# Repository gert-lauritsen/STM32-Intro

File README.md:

# STM32-Intro

Agenda
+ Grafisk opsætning
+ Debugger
+ Seriel kommunikation
+ SPI
+ Timer
+ ADC
+ USB

Eksemple 1 er en batterimåler, som vi bruger til at vise ADC og timer

Eksemple 2 er en temperaturlogger, som bruges til at demo USB og SPI

Udviklingsværktøjet er [STM32CUBEIDE](https://www.st.com/en/development-tools/stm32cubeide.html)

Det hele kan følges online på [YOUTUBE](https://youtu.be/U5xcWw9ncK8) og Zoom

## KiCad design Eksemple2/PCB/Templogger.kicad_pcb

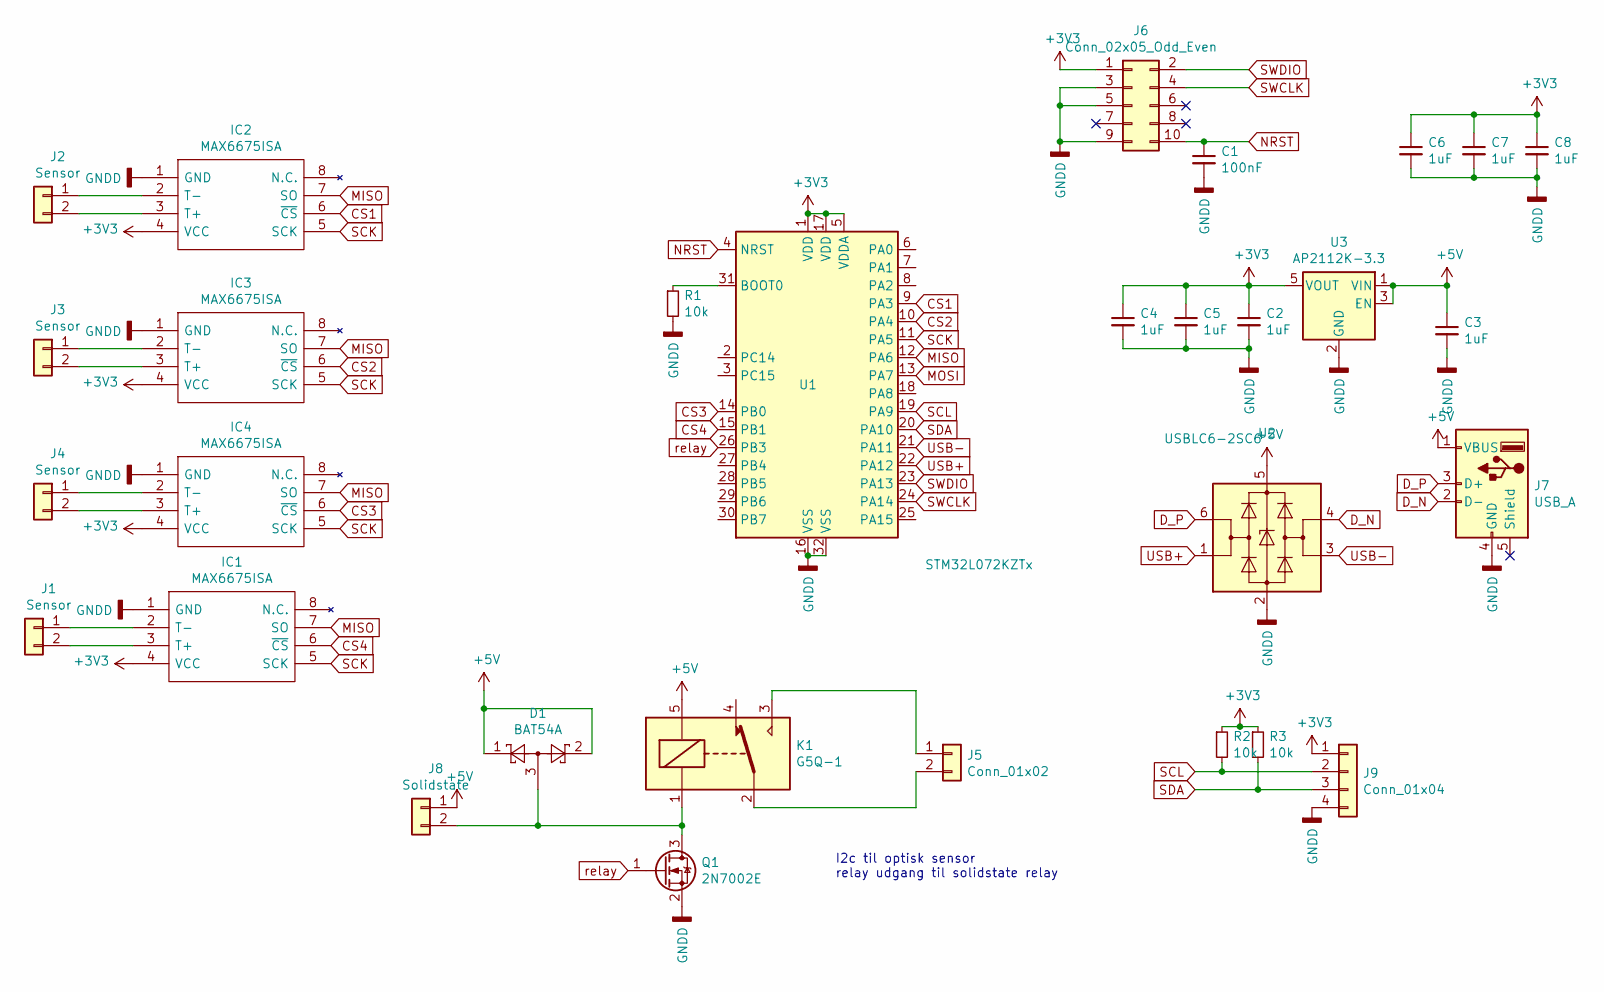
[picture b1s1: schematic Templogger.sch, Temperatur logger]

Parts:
C1: 100nF; C_0805_2012Metric
C2, C3, C4, C5, C6, C7, C8: 1uF; C_0805_2012Metric
D1: BAT54A; SOT-23
IC1, IC2, IC3, IC4: MAX6675ISA; SOIC127P600X175-8N; Mouser Part Number N/A
J1, J2, J3, J4: Sensor; Molex_KK-254_AE-6410-02A_1x02_P2.54mm_Vertical
J5: Conn_01x02; PhoenixContact_MSTBVA_2,5_2-G_1x02_P5.00mm_Vertical
J6: Conn_02x05_Odd_Even; PinHeader_2x05_P1.27mm_Vertical_SMD
J7: USB_A; USB_Mini-B_Wuerth_65100516121_Horizontal
J8: Solidstate; Molex_KK-254_AE-6410-02A_1x02_P2.54mm_Vertical
J9: Conn_01x04; Molex_SL_171971-0004_1x04_P2.54mm_Vertical
K1: G5Q-1; Relay_SPDT_Omron-G5Q-1
Q1: 2N7002E; SOT-23
R1, R2, R3: 10k; R_0805_2012Metric
U1: STM32L072KZTx; LQFP-32_7x7mm_P0.8mm
U2: USBLC6-2SC6; SOT-23-6
U3: AP2112K-3.3; SOT-23-5

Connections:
+3V3: C2.1, C4.1, C5.1, C6.1, C7.1, C8.1, IC1.4 (VCC), IC2.4 (VCC), IC3.4 (VCC), IC4.4 (VCC), J6.1, J9.1, R2.1, R3.1, U1.1 (VDD), U1.5 (VDDA), U1.17 (VDD), U3.5 (VOUT)
+5V: C3.1, D1.1, D1.2, J7.1 (VBUS), J8.1, K1.5, U2.5 (VBUS), U3.1 (VIN), U3.3 (EN)
CS1: IC2.6 (~CS), U1.9 (PA3)
CS2: IC3.6 (~CS), U1.10 (PA4)
CS3: IC4.6 (~CS), U1.14 (PB0)
CS4: IC1.6 (~CS), U1.15 (PB1)
D_N: J7.2 (D-), U2.4 (I/O2)
D_P: J7.3 (D+), U2.6 (I/O1)
GNDD: C1.2, C2.2, C3.2, C4.2, C5.2, C6.2, C7.2, C8.2, IC1.1 (GND), IC2.1 (GND), IC3.1 (GND), IC4.1 (GND), J6.3, J6.5, J6.9, J7.4 (GND), J9.4, Q1.2 (S), R1.2, U1.16 (VSS), U1.32 (VSS), U2.2 (GND), U3.2 (GND)
MISO: IC1.7 (SO), IC2.7 (SO), IC3.7 (SO), IC4.7 (SO), U1.12 (PA6)
NRST: C1.1, J6.10, U1.4 (NRST)
unnamed: D1.3, J8.2, K1.1, Q1.3 (D)
unnamed: IC1.2 (T-), J1.1
unnamed: IC1.3 (T+), J1.2
unnamed: IC2.2 (T-), J2.1
unnamed: IC2.3 (T+), J2.2
unnamed: IC3.2 (T-), J3.1
unnamed: IC3.3 (T+), J3.2
unnamed: IC4.2 (T-), J4.1
unnamed: IC4.3 (T+), J4.2
unnamed: J5.1, K1.3
unnamed: J5.2, K1.2
unnamed: R1.1, U1.31 (BOOT0)
SCK: IC1.5 (SCK), IC2.5 (SCK), IC3.5 (SCK), IC4.5 (SCK), U1.11 (PA5)
SCL: J9.2, R2.2, U1.19 (PA9)
SDA: J9.3, R3.2, U1.20 (PA10)
SWCLK: J6.4, U1.24 (PA14)
SWDIO: J6.2, U1.23 (PA13)
USB+: U1.22 (PA12), U2.1 (I/O1)
USB-: U1.21 (PA11), U2.3 (I/O2)
relay: Q1.1 (G), U1.26 (PB3)

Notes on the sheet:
I2c til optisk sensor relay udgang til solidstate relay

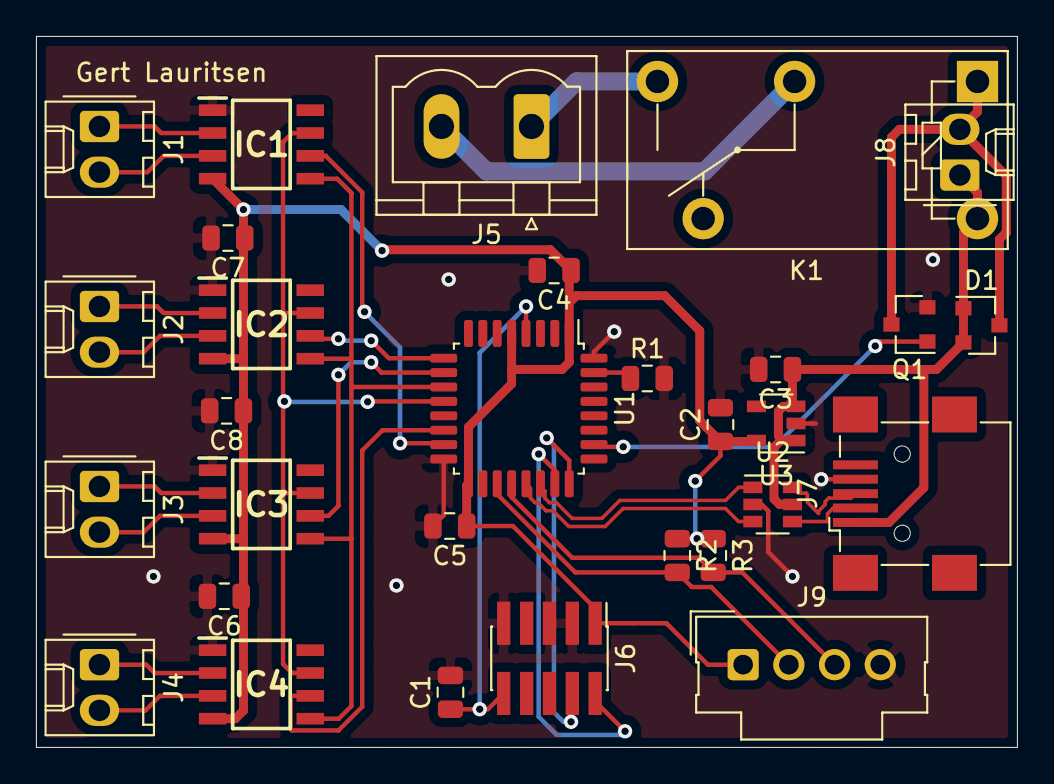
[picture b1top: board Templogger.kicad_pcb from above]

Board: 2 copper layers, 54.5 x 39.5 mm, 30 parts (0 on the bottom side), 31 nets.

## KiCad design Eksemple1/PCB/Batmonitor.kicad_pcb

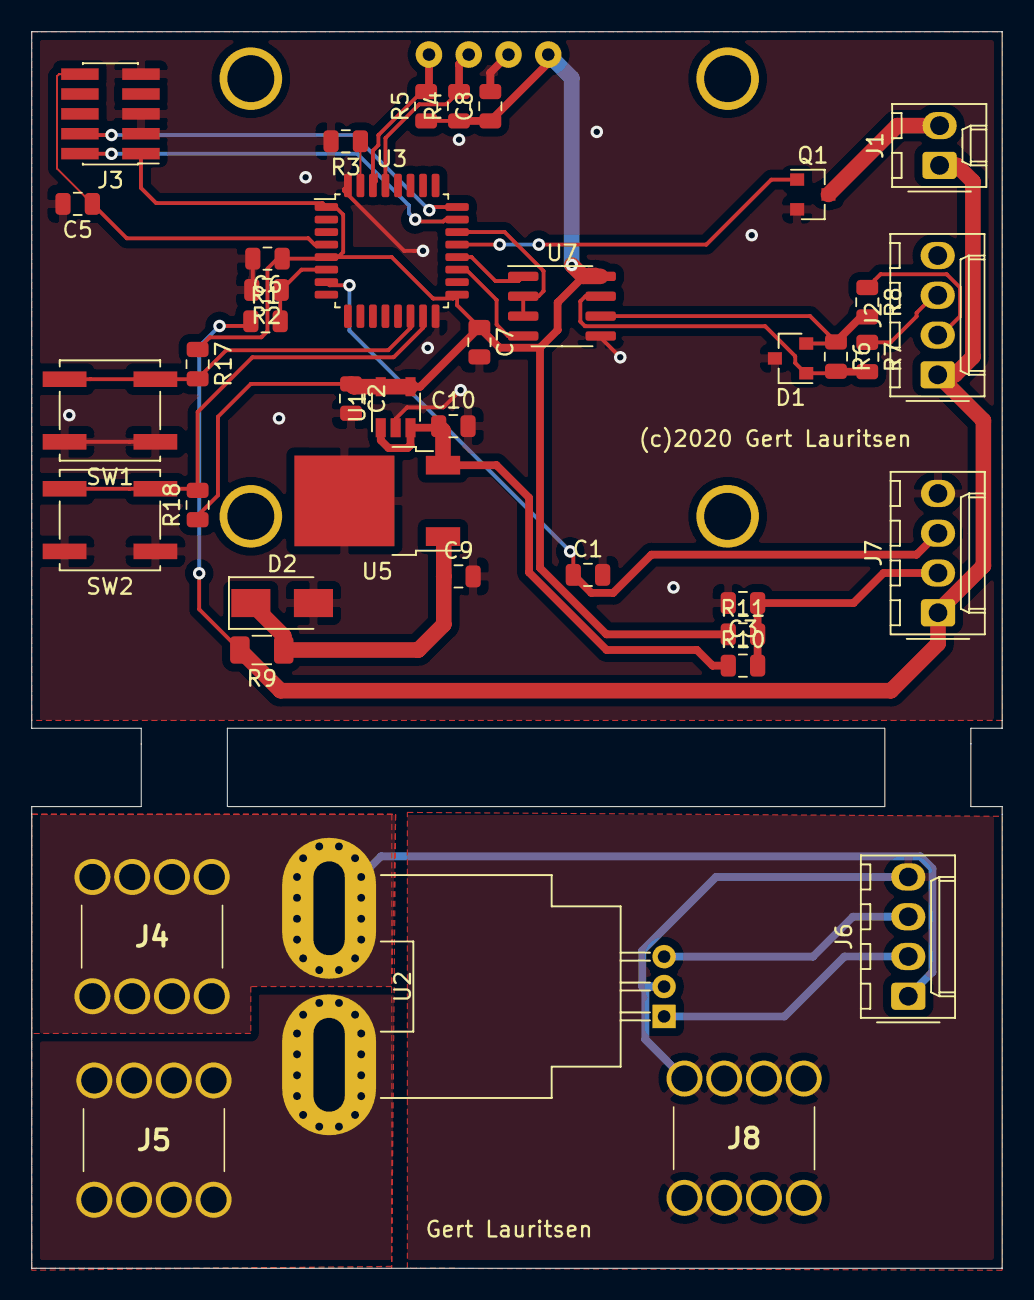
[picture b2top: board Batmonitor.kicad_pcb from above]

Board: 2 copper layers, 62.0 x 79.0 mm, 41 parts (1 on the bottom side), 30 nets.

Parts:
C1, C5: 100nF; C_0805_2012Metric
C2: 22uF; C_0805_2012Metric
C3, C6, C7, C8, C10: 1uF; C_0805_2012Metric
C9: 2.2uF; C_0805_2012Metric
D1: SM712_TCT; SOT-23
D2: SMZZ33-TP; D_SMA
J1: Alarm; Molex_KK-254_AE-6410-02A_1x02_P2.54mm_Vertical
J2, J6, J7: Conn_01x04; Molex_KK-254_AE-6410-04A_1x04_P2.54mm_Vertical
J3: Prog; PinHeader_2x05_P1.27mm_Vertical_SMD
J4, J5, J8: Conn_01x01; 7460307
Q1: Sq2318AES; SOT-23
R1: 100k; R_0805_2012Metric
R2, R3, R4, R5, R17, R18: 10k; R_0805_2012Metric
R6: 1k; R_0805_2012Metric
R7, R8: 100R; R_0805_2012Metric
R9: 1R; R_1206_3216Metric
R10: NM; R_0805_2012Metric
R11: 0R; R_0805_2012Metric
SW1, SW2: SW_Push; SW_Push_1P1T_NO_CK_KSC7xxJ
U1: ADP7142AUJZ; TSOT-23-5
U2: ACS770xCB-100B-PFF; Allegro_CB_PFF
U3: STM32L052K8Tx; LQFP-32_7x7mm_P0.8mm
U4: OLED128x64; 1.3 IIC display
U5: LM78M05_TO252; TO-252-2
U7: MAX3078E; SOIC-8_3.9x4.9mm_P1.27mm

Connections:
+3V3: C2.1, C6.1, C7.1, C8.1, J3.1, R4.1, R5.1, R11.1, R17.1, R18.1, U1.4, U1.5, U3.1, U3.5, U3.17, U4.1, U7.8
+5V: C10.1, R10.1, U1.1, U1.3, U5.3
+BATT: J1.1, J2.1, J7.1, R1.1, R9.2
+Ibat: C1.1, J7.3, U3.7
Buzz: Q1.1, U3.21
DIR: U3.22, U7.2, U7.3
GNDD: C1.2, C2.2, C3.2, C5.2, C6.2, C7.2, C8.2, C9.2, C10.2, D1.3, D2.2, J3.3, J3.5, J3.9, J7.4, Q1.2, R2.2, R3.2, SW1.2, SW2.2, U1.2, U3.16, U3.32, U4.2, U5.2, U7.5
Knap1: R17.2, SW1.1, U3.14
Knap2: R18.2, SW2.1, U3.15
unnamed: C3.1, J7.2, R10.2, R11.2
unnamed: C9.1, D2.1, R9.1, U5.1
unnamed: D1.1, R6.2, R7.2, U7.7
unnamed: D1.2, R6.1, R8.2, U7.6
unnamed: J1.2, Q1.3
unnamed: J2.2, R8.1
unnamed: J2.3, R7.1
unnamed: J4.1, J6.1, U2.4
unnamed: J5.1, U2.5
unnamed: J6.2, U2.1
unnamed: J6.3, U2.3
unnamed: J6.4, J8.1, U2.2
unnamed: R3.1, U3.31
RST: C5.1, J3.10, U3.4
RX: U3.20, U7.1
SCL: R4.2, U3.29, U4.3
SDA: R5.2, U3.30, U4.4
SWDCLK: J3.4, U3.24
SWDIO: J3.2, U3.23
TX: U3.19, U7.4
Vbat: R1.2, R2.1, U3.6

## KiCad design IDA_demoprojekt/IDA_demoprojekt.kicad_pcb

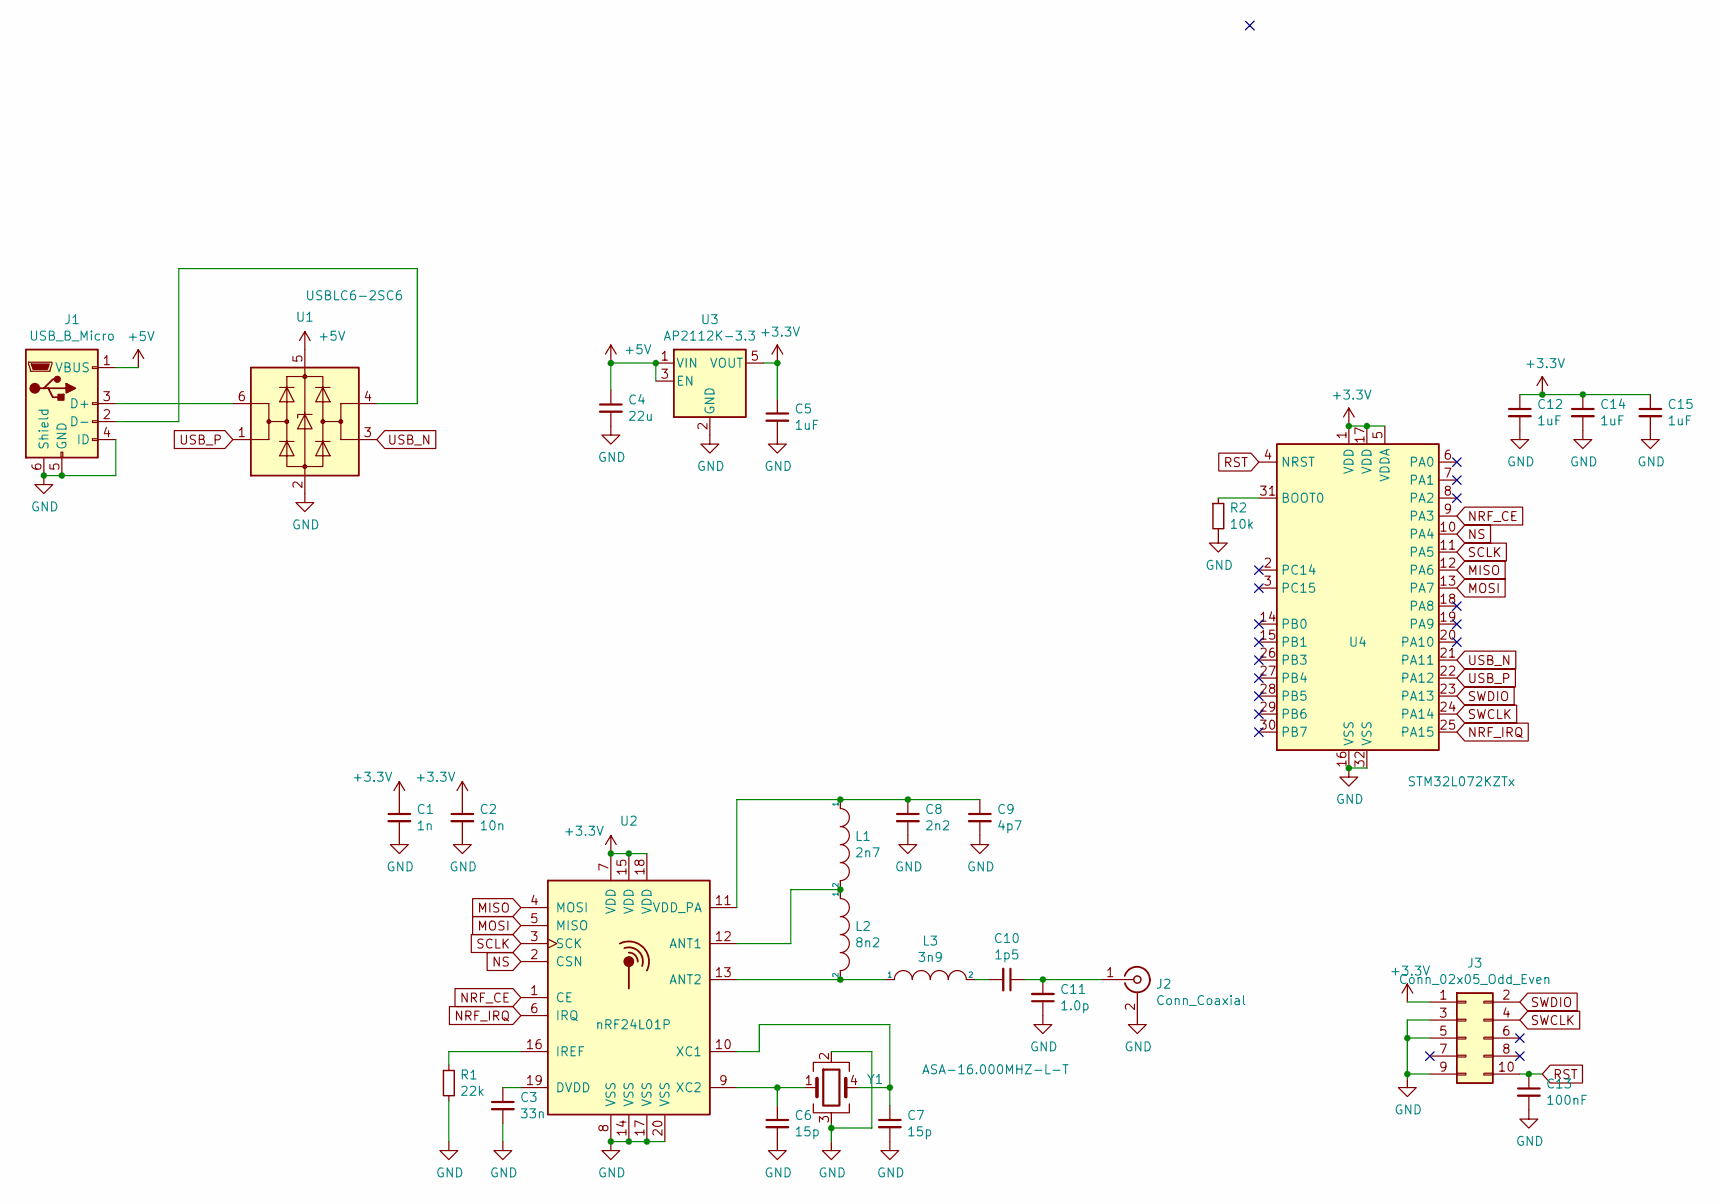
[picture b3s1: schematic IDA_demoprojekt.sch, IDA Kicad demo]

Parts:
C1: 1n; C_0402_1005Metric
C2: 10n; C_0402_1005Metric
C3: 33n; C_0402_1005Metric
C4: 22u; C_0805_2012Metric
C5, C12, C14, C15: 1uF; C_0805_2012Metric
C6, C7: 15p; C_0402_1005Metric
C8: 2n2; C_0402_1005Metric
C9: 4p7; C_0402_1005Metric
C10: 1p5; C_0402_1005Metric
C11: 1.0p; C_0402_1005Metric
C13: 100nF; C_0805_2012Metric
J1: USB_B_Micro; USB_Mini-B_Wuerth_65100516121_Horizontal
J2: Conn_Coaxial; SMA_Amphenol_132134-14_Vertical
J3: Conn_02x05_Odd_Even; PinHeader_2x05_P1.27mm_Vertical_SMD
L1: 2n7; L_0402_1005Metric
L2: 8n2; L_0402_1005Metric
L3: 3n9; L_0402_1005Metric
R1: 22k; R_0402_1005Metric
R2: 10k; R_0402_1005Metric
U1: USBLC6-2SC6; SOT-23-6
U2: nRF24L01P; QFN-20-1EP_4x4mm_P0.5mm_EP2.6x2.6mm
U3: AP2112K-3.3; SOT-23-5
U4: STM32L072KZTx; LQFP-32_7x7mm_P0.8mm
Y1: ASA-16.000MHZ-L-T; Crystal_SMD_2016-4Pin_2.0x1.6mm

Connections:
+3V3: C1.1, C2.1, C5.1, C12.1, C14.1, C15.1, J3.1, U2.7 (VDD), U2.15 (VDD), U2.18 (VDD), U3.5 (VOUT), U4.1 (VDD), U4.5 (VDDA), U4.17 (VDD)
+5V: C4.1, J1.1 (VBUS), U1.5 (VBUS), U3.1 (VIN), U3.3 (EN)
GND: C1.2, C2.2, C3.2, C4.2, C5.2, C6.2, C7.2, C8.2, C9.2, C11.1, C12.2, C13.2, C14.2, C15.2, J1.4 (ID), J1.5 (GND), J1.6 (Shield), J2.2 (Ext), J3.3, J3.5, J3.9, R1.2, R2.2, U1.2 (GND), U2.8 (VSS), U2.14 (VSS), U2.17 (VSS), U2.20 (VSS), U3.2 (GND), U4.16 (VSS), U4.32 (VSS), Y1.2, Y1.3
MISO: U2.4 (MOSI), U4.12 (PA6)
MOSI: U2.5 (MISO), U4.13 (PA7)
NRF_CE: U2.1 (CE), U4.9 (PA3)
NRF_IRQ: U2.6 (IRQ), U4.25 (PA15)
NS: U2.2 (CSN), U4.10 (PA4)
unnamed: C3.1, U2.19 (DVDD)
unnamed: C6.1, U2.9 (XC2), Y1.1
unnamed: C7.1, U2.10 (XC1), Y1.4
unnamed: C8.1, C9.1, L1.1, U2.11 (VDD_PA)
unnamed: C10.1, C11.2, J2.1 (In)
unnamed: C10.2, L3.2
unnamed: J1.2 (D-), U1.4 (I/O2)
unnamed: J1.3 (D+), U1.6 (I/O1)
unnamed: L1.2, L2.1, U2.12 (ANT1)
unnamed: L2.2, L3.1, U2.13 (ANT2)
unnamed: R1.1, U2.16 (IREF)
unnamed: R2.1, U4.31 (BOOT0)
RST: C13.1, J3.10, U4.4 (NRST)
SCLK: U2.3 (SCK), U4.11 (PA5)
SWCLK: J3.4, U4.24 (PA14)
SWDIO: J3.2, U4.23 (PA13)
USB_N: U1.3 (I/O2), U4.21 (PA11)
USB_P: U1.1 (I/O1), U4.22 (PA12)

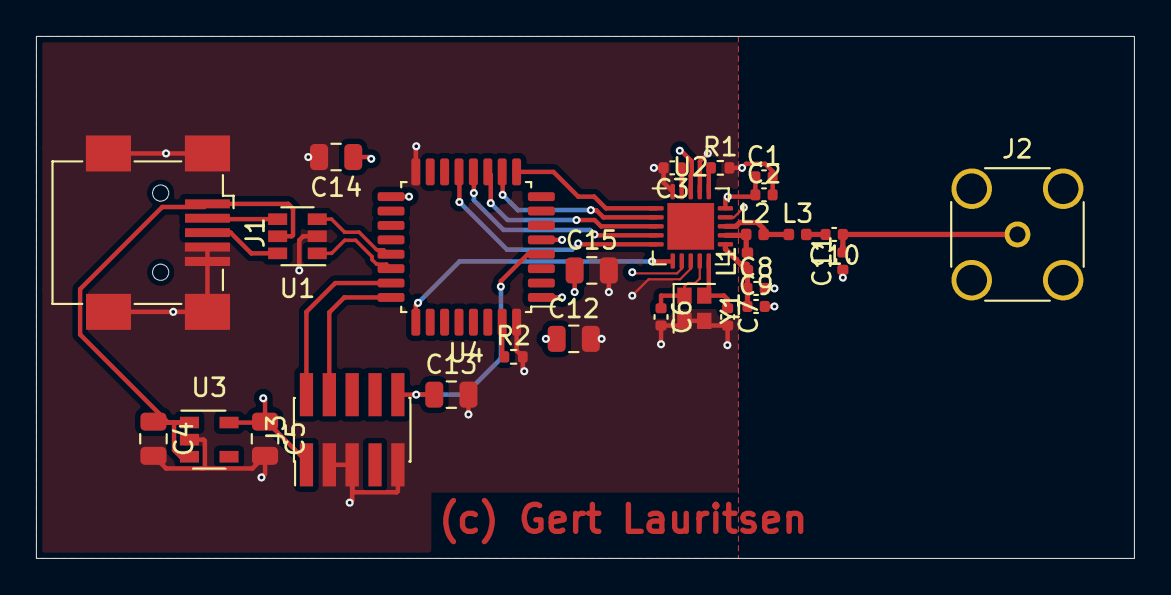
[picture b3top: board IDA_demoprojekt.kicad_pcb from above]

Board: 4 copper layers, 61.0 x 29.0 mm, 28 parts (0 on the bottom side), 26 nets.

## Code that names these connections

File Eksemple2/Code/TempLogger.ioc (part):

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Mcu.Name=STM32L072K(B-Z)Tx
Mcu.Package=LQFP32
Mcu.UserName=STM32L072KZTx
PA10.Mode=I2C
PA10.Signal=I2C1_SDA
PA11.Mode=Device
PA11.Signal=USB_DM
PA12.Mode=Device
PA12.Signal=USB_DP
PA13.Mode=Serial_Wire
PA13.Signal=SYS_SWDIO
PA14.Mode=Serial_Wire
PA14.Signal=SYS_SWCLK
PA3.GPIOParameters=PinState,GPIO_Label
PA3.GPIO_Label=CS1
PA3.PinState=GPIO_PIN_SET
PA3.Signal=GPIO_Output
PA4.GPIOParameters=PinState,GPIO_Label
PA4.GPIO_Label=CS2
PA4.PinState=GPIO_PIN_SET
PA4.Signal=GPIO_Output
PA5.Mode=Full_Duplex_Master
PA5.Signal=SPI1_SCK
PA6.Mode=Full_Duplex_Master
PA6.Signal=SPI1_MISO
PA7.Mode=Full_Duplex_Master
PA7.Signal=SPI1_MOSI
PA9.Mode=I2C
PA9.Signal=I2C1_SCL
PB0.GPIOParameters=PinState,GPIO_Label
PB0.GPIO_Label=CS3
PB0.PinState=GPIO_PIN_SET
PB0.Signal=GPIO_Output
PB1.GPIOParameters=PinState,GPIO_Label
PB1.GPIO_Label=CS4
PB1.PinState=GPIO_PIN_SET
PB1.Signal=GPIO_Output
PB3.GPIOParameters=GPIO_Label
PB3.GPIO_Label=Relay
PB3.Signal=GPIO_Output
RCC.SYSCLKFreq_VALUE=32000000
RCC.SYSCLKSource=RCC_SYSCLKSOURCE_PLLCLK
board=custom

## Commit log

2021-01-28 Create STM32 Intro.pptx
    Init
2021-02-21 SChematic lagt ind
2021-03-04 tilføjet eksempler
2021-03-09 Create STM32 Intro Incl Video.pptx
    Powerpoint med video

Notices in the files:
Eksemple1/PCB/Batmonitor.kicad_pcb:
(c)2020 Gert Lauritsen
